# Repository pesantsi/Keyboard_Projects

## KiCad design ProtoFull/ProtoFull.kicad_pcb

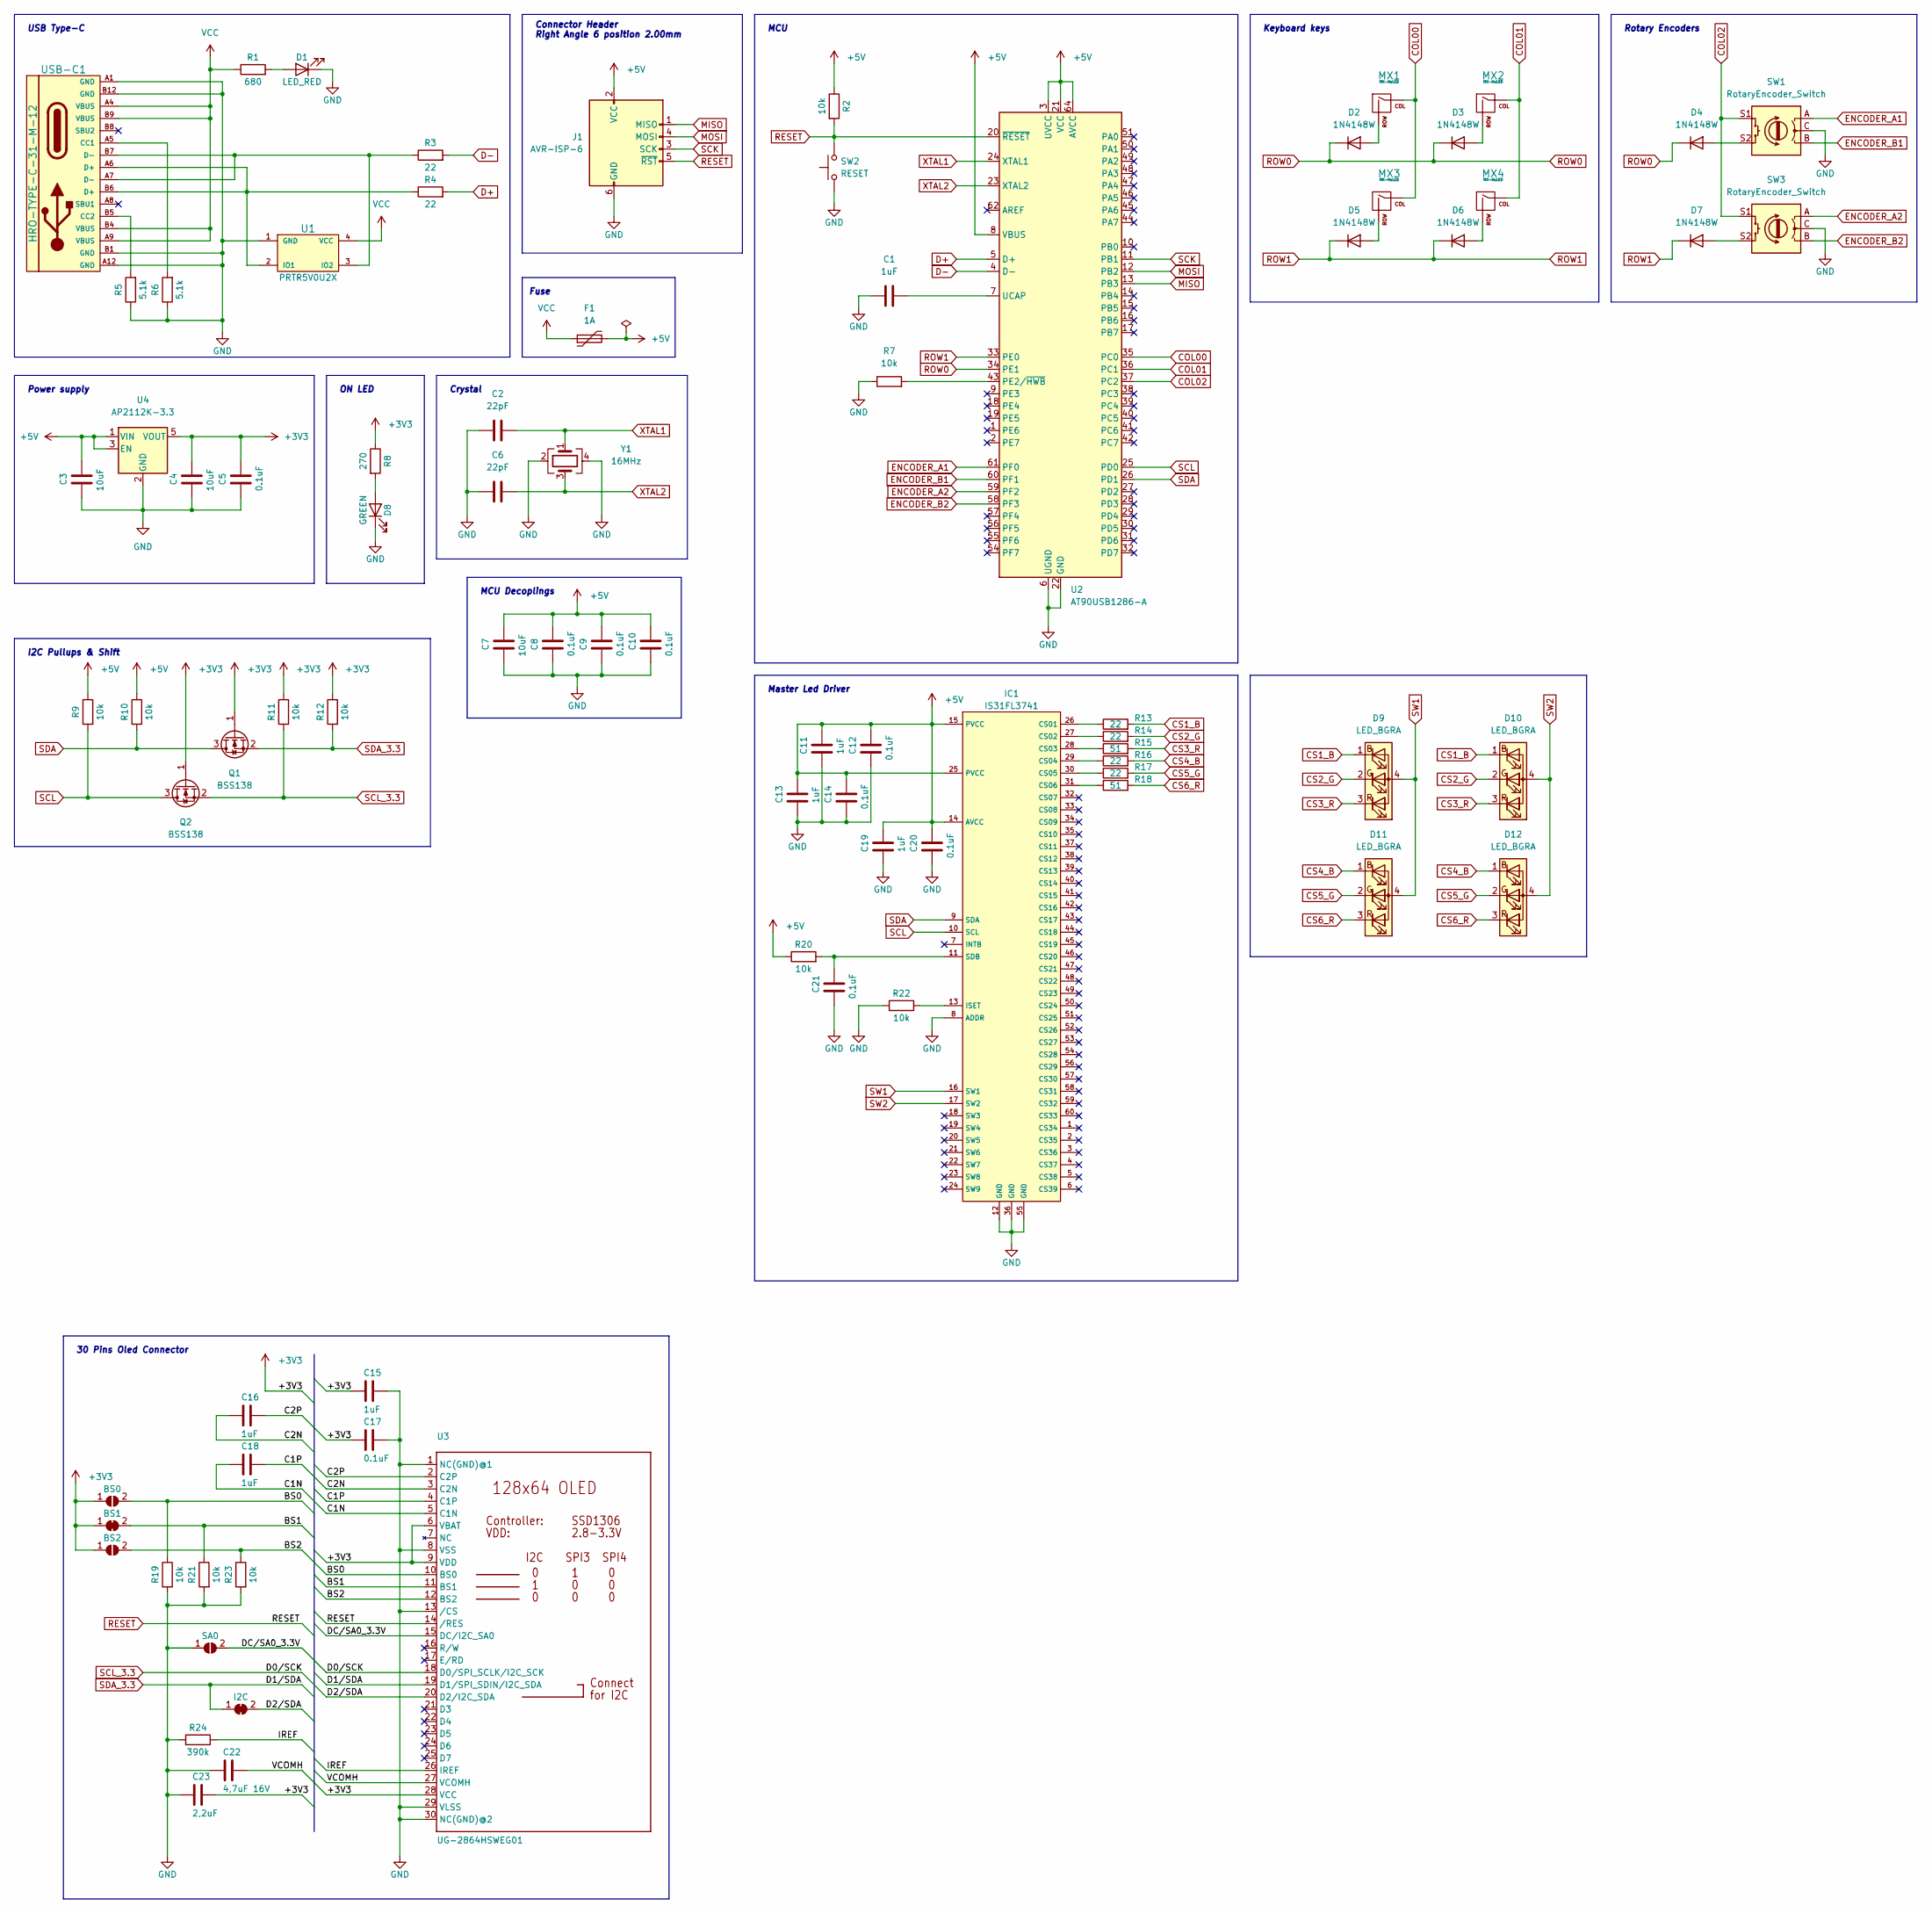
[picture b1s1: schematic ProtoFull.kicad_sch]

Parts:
C1, C11, C13, C19: 1uF; C_0805_2012Metric
C2, C6: 22pF; C_0805_2012Metric
C3, C4, C7: 10uF; C_0805_2012Metric
C5, C8, C9, C10, C12, C14, C20, C21: 0.1uF; C_0805_2012Metric
C15, C16, C18: 1uF; C_0805_2012Metric_Pad1.18x1.45mm_HandSolder
C17: 0.1uF; C_0805_2012Metric_Pad1.18x1.45mm_HandSolder
C22: 4,7uF 16V; C_0805_2012Metric_Pad1.18x1.45mm_HandSolder
C23: 2,2uF; C_0805_2012Metric_Pad1.18x1.45mm_HandSolder
D1: LED_RED; LED_0805_2012Metric_Pad1.15x1.40mm_HandSolder
D2, D3, D4, D5, D6, D7: 1N4148W; D_SOD-123
D8: GREEN; LED_0805_2012Metric_Pad1.15x1.40mm_HandSolder
D9, D10, D11, D12: LED_BGRA; QBLP677R-RGB
F1: 1A; Fuse_1206_3216Metric_Pad1.42x1.75mm_HandSolder
IC1: IS31FL3741; QFN40P700X700X80-61N-D
J1: AVR-ISP-6; Reset_Pretty
JP1: BS0; SolderJumper-2_P1.3mm_Open_RoundedPad1.0x1.5mm
JP2: BS1; SolderJumper-2_P1.3mm_Open_RoundedPad1.0x1.5mm
JP3: BS2; SolderJumper-2_P1.3mm_Open_RoundedPad1.0x1.5mm
JP4: SA0; SolderJumper-2_P1.3mm_Open_RoundedPad1.0x1.5mm
JP5: I2C; SolderJumper-2_P1.3mm_Bridged_RoundedPad1.0x1.5mm
MX1, MX2, MX3, MX4: MX-NoLED; MXOnly-1U-NoLED
Q1, Q2: BSS138; SOT-23
R1: 680; R_0805_2012Metric
R2, R7, R9, R10, R11, R12, R20, R22: 10k; R_0805_2012Metric
R3, R4, R13, R14, R16, R17: 22; R_0805_2012Metric
R5, R6: 5.1k; R_0805_2012Metric
R8: 270; R_0805_2012Metric
R15, R18: 51; R_0805_2012Metric
R19, R21, R23: 10k; R_0805_2012Metric_Pad1.20x1.40mm_HandSolder
R24: 390k; R_0805_2012Metric_Pad1.20x1.40mm_HandSolder
SW1, SW3: RotaryEncoder_Switch; RotaryEncoder_Alps_EC12E-Switch_Vertical_H20mm_CircularMoun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
SW2: RESET; PushButton_6x6mm_TH
U1: PRTR5V0U2X; SOT-143_Handsoldering
U2: AT90USB1286-A; TQFP-64_14x14mm_P0.8mm
U3: UG-2864HSWEG01; 5051103091
U4: AP2112K-3.3; SOT-23-5
USB-C1: HRO-TYPE-C-31-M-12; TYPE-C-31-M-12
Y1: 16MHz; Crystal_SMD_3225-4Pin_3.2x2.5mm_HandSoldering

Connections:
+3V3: C4.1, C5.1, C15.2, C17.2, C23.1, JP1.1 (A), JP2.1 (A), JP3.1 (A), Q1.1 (G), Q2.1 (G), R8.1, R11.1, R12.1, U3.6 (VBAT), U3.9 (VDD), U3.28 (VCC), U4.5 (VOUT)
+5V: C3.1, C7.1, C8.1, C9.1, C10.1, C11.1, C12.1, C13.1, C14.1, C19.1, C20.1, F1.2, IC1.14 (AVCC), IC1.15 (PVCC), IC1.25 (PVCC), J1.2 (VCC), R2.1, R9.1, R10.1, R20.1, U2.3 (UVCC), U2.8 (VBUS), U2.21 (VCC), U2.52 (VCC), U2.64 (AVCC), U4.1 (VIN), U4.3 (EN)
/BS0: JP1.2 (B), R19.1, U3.10 (BS0)
/BS1: JP2.2 (B), R21.1, U3.11 (BS1)
/BS2: JP3.2 (B), R23.1, U3.12 (BS2)
/C1N: C18.2, U3.5 (C1N)
/C1P: C18.1, U3.4 (C1P)
/C2N: C16.2, U3.3 (C2N)
/C2P: C16.1, U3.2 (C2P)
/D2/SDA: JP5.2 (B), U3.20 (D2/I2C_SDA)
/DC/SA0_3.3V: JP4.2 (B), U3.15 (DC/I2C_SA0)
/IREF: R24.1, U3.26 (IREF)
/VCOMH: C22.1, U3.27 (VCOMH)
COL00: MX1.1 (COL), MX3.1 (COL), U2.35 (PC0)
COL01: MX2.1 (COL), MX4.1 (COL), U2.36 (PC1)
COL02: SW1.S1, SW3.S1, U2.37 (PC2)
CS1_B: D9.1 (BK), D10.1 (BK), R13.2
CS2_G: D9.2 (GK), D10.2 (GK), R14.2
CS3_R: D9.3 (RK), D10.3 (RK), R15.2
CS4_B: D11.1 (BK), D12.1 (BK), R16.2
CS5_G: D11.2 (GK), D12.2 (GK), R17.2
CS6_R: D11.3 (RK), D12.3 (RK), R18.2
D+: R4.2, U2.5 (D+)
D-: R3.2, U2.4 (D-)
ENCODER_A1: SW1.A, U2.61 (PF0)
ENCODER_A2: SW3.A, U2.59 (PF2)
ENCODER_B1: SW1.B, U2.60 (PF1)
ENCODER_B2: SW3.B, U2.58 (PF3)
GND: C1.2, C2.1, C3.2, C4.2, C5.2, C6.1, C7.2, C8.2, C9.2, C10.2, C11.2, C12.2, C13.2, C14.2, C15.1, C17.1, C19.2, C20.2, C21.2, C22.2, C23.2, D1.1 (K), D8.1 (K), IC1.8 (ADDR), IC1.12 (GND), IC1.36 (GND), IC1.55 (GND), J1.6 (GND), JP4.1 (A), R5.1, R6.1, R7.1, R19.2, R21.2, R22.2, R23.2, R24.2, SW1.C, SW2.1, SW3.C, U1.1 (GND), U2.6 (UGND), U2.22 (GND), U2.53 (GND), U2.63 (GND), U3.1 (NC(GND)@1), U3.8 (VSS), U3.13 (/CS), U3.29 (VLSS), U3.30 (NC(GND)@2), U4.2 (GND), USB-C1.A1 (GND), USB-C1.A12 (GND), USB-C1.B1 (GND), USB-C1.B12 (GND), Y1.2, Y1.4
MISO: J1.1 (MISO), U2.13 (PB3)
MOSI: J1.4 (MOSI), U2.12 (PB2)
unnamed: C1.1, U2.7 (UCAP)
unnamed: C21.1, IC1.11 (SDB), R20.2
unnamed: D1.2 (A), R1.2
unnamed: D2.2 (A), MX1.2 (ROW)
unnamed: D3.2 (A), MX2.2 (ROW)
unnamed: D4.2 (A), SW1.S2
unnamed: D5.2 (A), MX3.2 (ROW)
unnamed: D6.2 (A), MX4.2 (ROW)
unnamed: D7.2 (A), SW3.S2
unnamed: D8.2 (A), R8.2
unnamed: IC1.13 (ISET), R22.1
unnamed: IC1.26 (CS01), R13.1
unnamed: IC1.27 (CS02), R14.1
unnamed: IC1.28 (CS03), R15.1
unnamed: IC1.29 (CS04), R16.1
unnamed: IC1.30 (CS05), R17.1
unnamed: IC1.31 (CS06), R18.1
unnamed: R3.1, U1.3 (IO2), USB-C1.A7 (D-), USB-C1.B7 (D-)
unnamed: R4.1, U1.2 (IO1), USB-C1.A6 (D+), USB-C1.B6 (D+)
unnamed: R5.2, USB-C1.B5 (CC2)
unnamed: R6.2, USB-C1.A5 (CC1)
unnamed: R7.2, U2.43 (PE2/~HWB)
RESET: J1.5 (~RST), R2.2, SW2.2, U2.20 (~RESET), U3.14 (/RES)
ROW0: D2.1 (K), D3.1 (K), D4.1 (K), U2.34 (PE1)
ROW1: D5.1 (K), D6.1 (K), D7.1 (K), U2.33 (PE0)
SCK: J1.3 (SCK), U2.11 (PB1)
SCL: IC1.10 (SCL), Q2.3 (D), R9.2, U2.25 (PD0)
SCL_3.3: Q2.2 (S), R11.2, U3.18 (D0/SPI_SCLK/I2C_SCK)
SDA: IC1.9 (SDA), Q1.3 (D), R10.2, U2.26 (PD1)
SDA_3.3: JP5.1 (A), Q1.2 (S), R12.2, U3.19 (D1/SPI_SDIN/I2C_SDA)
SW1: D9.4 (A), D11.4 (A), IC1.16 (SW1)
SW2: D10.4 (A), D12.4 (A), IC1.17 (SW2)
VCC: F1.1, R1.1, U1.4 (VCC), USB-C1.A4 (VBUS), USB-C1.A9 (VBUS), USB-C1.B4 (VBUS), USB-C1.B9 (VBUS)
XTAL1: C2.2, U2.24 (XTAL1), Y1.1
XTAL2: C6.2, U2.23 (XTAL2), Y1.3

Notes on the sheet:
USB Type-C
Rotary Encoders
MCU Decoplings
I2C Pullups & Shift
ON LED
Fuse
Keyboard keys
Connector Header Right Angle 6 position 2.00mm
MCU
Crystal
Power supply
Master Led Driver
30 Pins Oled Connector

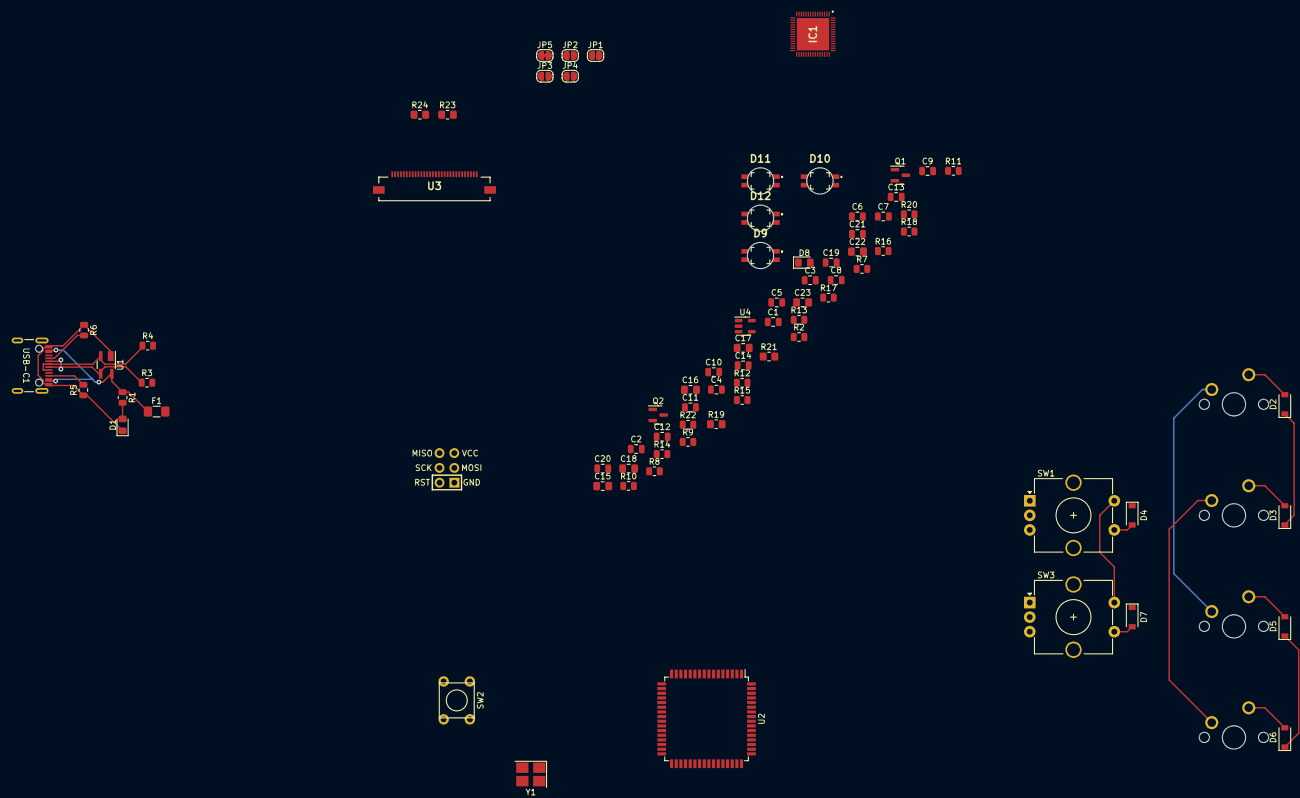
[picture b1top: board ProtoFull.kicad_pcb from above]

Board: 2 copper layers, 82 parts (0 on the bottom side), 66 nets.

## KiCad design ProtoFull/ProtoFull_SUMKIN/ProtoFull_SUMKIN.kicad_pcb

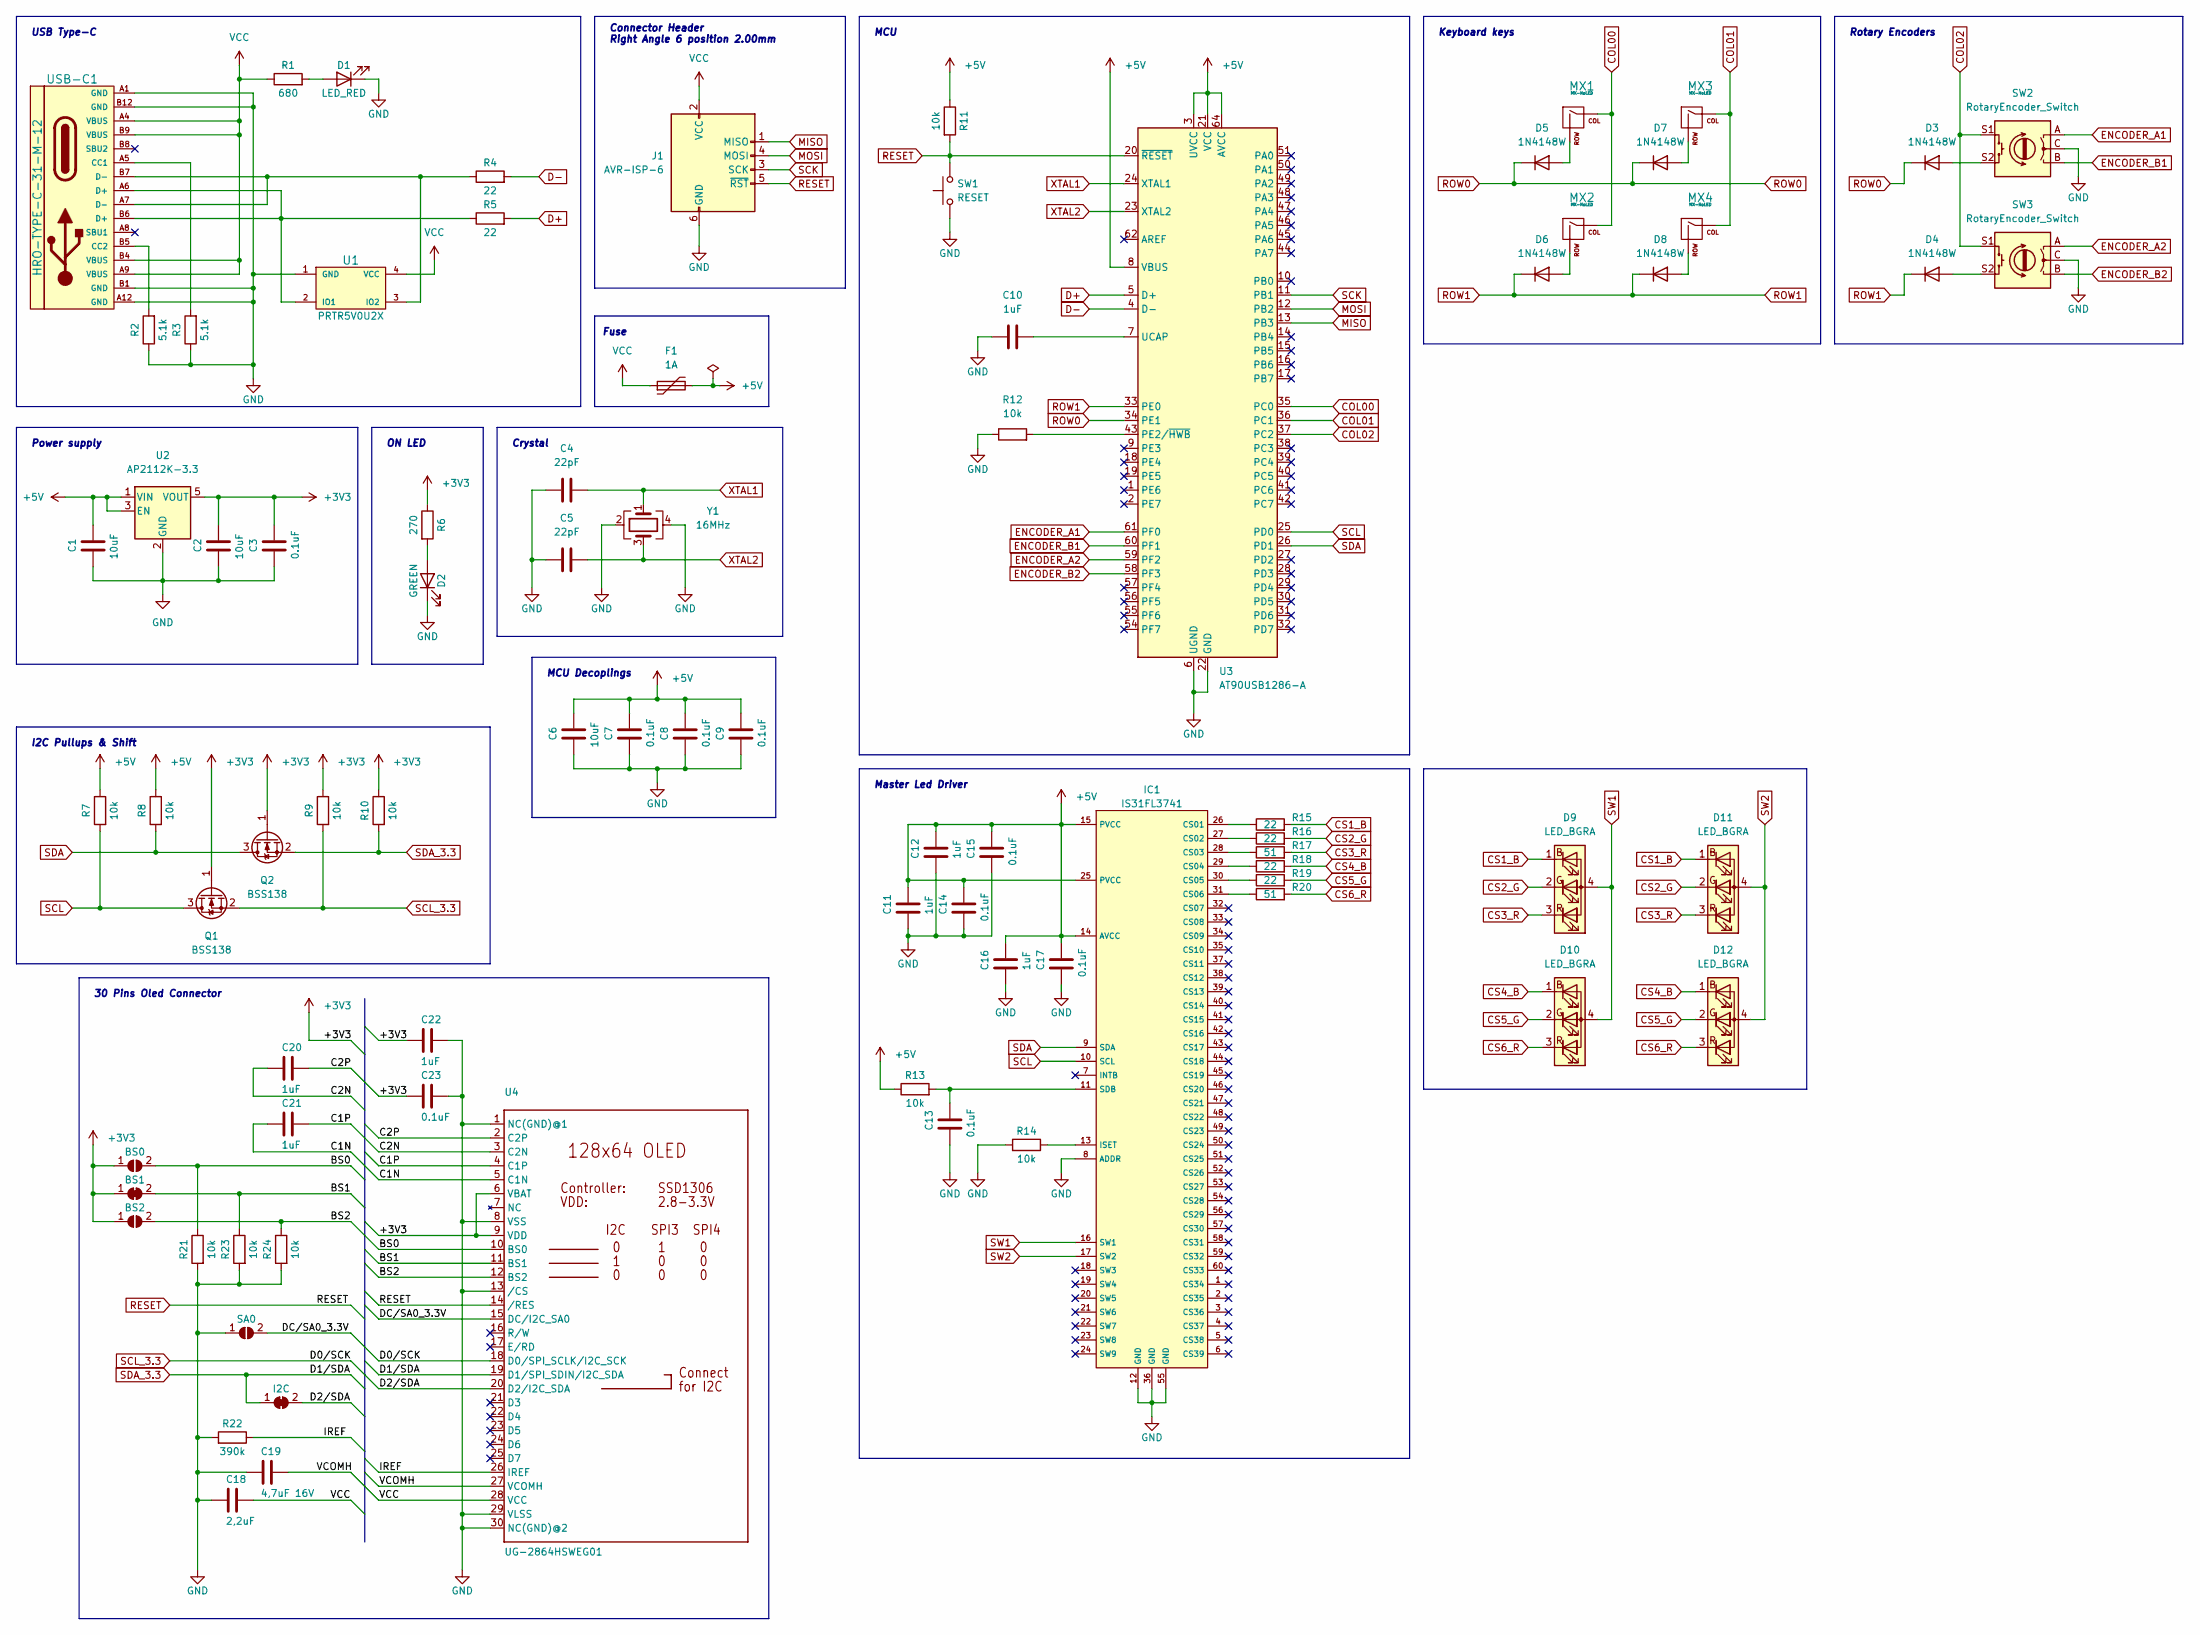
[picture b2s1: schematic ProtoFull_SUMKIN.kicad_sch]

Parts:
C1, C2, C6: 10uF; C_0805_2012Metric_Pad1.18x1.45mm_HandSolder
C3, C7, C8, C9, C13, C14, C15, C17, C23: 0.1uF; C_0805_2012Metric_Pad1.18x1.45mm_HandSolder
C4, C5: 22pF; C_0805_2012Metric_Pad1.18x1.45mm_HandSolder
C10, C11, C12, C16, C20, C21, C22: 1uF; C_0805_2012Metric_Pad1.18x1.45mm_HandSolder
C18: 2,2uF; C_0805_2012Metric_Pad1.18x1.45mm_HandSolder
C19: 4,7uF 16V; C_0805_2012Metric_Pad1.18x1.45mm_HandSolder
D1: LED_RED; LED_0805_2012Metric_Pad1.15x1.40mm_HandSolder
D2: GREEN; LED_0805_2012Metric_Pad1.15x1.40mm_HandSolder
D3, D4, D5, D6, D7, D8: 1N4148W; D_SOD-123
D9, D10, D11, D12: LED_BGRA; QBLP677R-RGB_RoundCutout
F1: 1A; Fuse_1206_3216Metric_Pad1.42x1.75mm_HandSolder
IC1: IS31FL3741; QFN-60_EP_7x7_Pitch0.4mm
J1: AVR-ISP-6; SWR204NRTND03STGA
JP1: BS0; SolderJumper-2_P1.3mm_Open_RoundedPad1.0x1.5mm
JP2: BS1; SolderJumper-2_P1.3mm_Open_RoundedPad1.0x1.5mm
JP3: BS2; SolderJumper-2_P1.3mm_Open_RoundedPad1.0x1.5mm
JP4: SA0; SolderJumper-2_P1.3mm_Open_RoundedPad1.0x1.5mm
JP5: I2C; SolderJumper-2_P1.3mm_Bridged_RoundedPad1.0x1.5mm
MX1, MX2, MX3, MX4: MX-NoLED; MXOnly-1U-NoLED
Q1, Q2: BSS138; SOT-23
R1: 680; R_0805_2012Metric
R2, R3: 5.1k; R_0805_2012Metric
R4, R5: 22; R_0805_2012Metric
R6: 270; R_0805_2012Metric
R7, R8, R9, R10: 10k; R_0805_2012Metric
R11, R12, R13, R14, R21, R23, R24: 10k; R_0805_2012Metric_Pad1.20x1.40mm_HandSolder
R15, R16, R18, R19: 22; R_0805_2012Metric_Pad1.20x1.40mm_HandSolder
R17, R20: 51; R_0805_2012Metric_Pad1.20x1.40mm_HandSolder
R22: 390k; R_0805_2012Metric_Pad1.20x1.40mm_HandSolder
SW1: RESET; SKQG-1155865
SW2, SW3: RotaryEncoder_Switch; RotaryEncoder_Alps_EC12E-Switch_Vertical_H20mm_CircularMoun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
U1: PRTR5V0U2X; SOT-143_Handsoldering
U2: AP2112K-3.3; SOT-23-5
U3: AT90USB1286-A; TQFP-64_14x14mm_P0.8mm
U4: UG-2864HSWEG01; 5051103091
USB-C1: HRO-TYPE-C-31-M-12; TYPE-C-31-M-12
Y1: 16MHz; Crystal_SMD_3225-4Pin_3.2x2.5mm_HandSoldering

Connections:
+3V3: C2.1, C3.1, C22.2, C23.2, JP1.1 (A), JP2.1 (A), JP3.1 (A), Q1.1 (G), Q2.1 (G), R6.1, R9.1, R10.1, U2.5 (VOUT), U4.6 (VBAT), U4.9 (VDD)
+5V: C1.1, C6.1, C7.1, C8.1, C9.1, F1.2, R7.1, R8.1, R11.1, R13.1, U2.1 (VIN), U2.3 (EN), U3.3 (UVCC), U3.8 (VBUS), U3.21 (VCC), U3.52 (VCC), U3.64 (AVCC)
/BS0: JP1.2 (B), R21.1, U4.10 (BS0)
/BS1: JP2.2 (B), R23.1, U4.11 (BS1)
/BS2: JP3.2 (B), R24.1, U4.12 (BS2)
/C1N: C21.2, U4.5 (C1N)
/C1P: C21.1, U4.4 (C1P)
/C2N: C20.2, U4.3 (C2N)
/C2P: C20.1, U4.2 (C2P)
/D2/SDA: JP5.2 (B), U4.20 (D2/I2C_SDA)
/DC/SA0_3.3V: JP4.2 (B), U4.15 (DC/I2C_SA0)
/IREF: R22.1, U4.26 (IREF)
/VCOMH: C19.1, U4.27 (VCOMH)
COL00: MX1.1 (COL), MX2.1 (COL), U3.35 (PC0)
COL01: MX3.1 (COL), MX4.1 (COL), U3.36 (PC1)
COL02: SW2.S1, SW3.S1, U3.37 (PC2)
CS1_B: D9.1 (BK), D11.1 (BK), R15.2
CS2_G: D9.2 (GK), D11.2 (GK), R16.2
CS3_R: D9.3 (RK), D11.3 (RK), R17.2
CS4_B: D10.1 (BK), D12.1 (BK), R18.2
CS5_G: D10.2 (GK), D12.2 (GK), R19.2
CS6_R: D10.3 (RK), D12.3 (RK), R20.2
D+: R5.2, U3.5 (D+)
D-: R4.2, U3.4 (D-)
ENCODER_A1: SW2.A, U3.61 (PF0)
ENCODER_A2: SW3.A, U3.59 (PF2)
ENCODER_B1: SW2.B, U3.60 (PF1)
ENCODER_B2: SW3.B, U3.58 (PF3)
GND: C1.2, C2.2, C3.2, C4.1, C5.1, C6.2, C7.2, C8.2, C9.2, C10.2, C11.2, C12.2, C13.2, C14.2, C15.2, C16.2, C17.2, C18.2, C19.2, C22.1, C23.1, D1.1 (K), D2.1 (K), IC1.8 (ADDR), IC1.12 (GND), IC1.36 (GND), IC1.55 (GND), J1.6 (GND), JP4.1 (A), R2.1, R3.1, R12.1, R14.2, R21.2, R22.2, R23.2, R24.2, SW1.1, SW2.C, SW3.C, U1.1 (GND), U2.2 (GND), U3.6 (UGND), U3.22 (GND), U3.53 (GND), U3.63 (GND), U4.1 (NC(GND)@1), U4.8 (VSS), U4.13 (/CS), U4.29 (VLSS), U4.30 (NC(GND)@2), USB-C1.A1 (GND), USB-C1.A12 (GND), USB-C1.B1 (GND), USB-C1.B12 (GND), Y1.2, Y1.4
MISO: J1.1 (MISO), U3.13 (PB3)
MOSI: J1.4 (MOSI), U3.12 (PB2)
unnamed: C10.1, U3.7 (UCAP)
unnamed: C13.1, IC1.11 (SDB), R13.2
unnamed: D1.2 (A), R1.2
unnamed: D2.2 (A), R6.2
unnamed: D3.2 (A), SW2.S2
unnamed: D4.2 (A), SW3.S2
unnamed: D5.2 (A), MX1.2 (ROW)
unnamed: D6.2 (A), MX2.2 (ROW)
unnamed: D7.2 (A), MX3.2 (ROW)
unnamed: D8.2 (A), MX4.2 (ROW)
unnamed: IC1.13 (ISET), R14.1
unnamed: IC1.26 (CS01), R15.1
unnamed: IC1.27 (CS02), R16.1
unnamed: IC1.28 (CS03), R17.1
unnamed: IC1.29 (CS04), R18.1
unnamed: IC1.30 (CS05), R19.1
unnamed: IC1.31 (CS06), R20.1
unnamed: R2.2, USB-C1.B5 (CC2)
unnamed: R3.2, USB-C1.A5 (CC1)
unnamed: R4.1, U1.3 (IO2), USB-C1.A7 (D-), USB-C1.B7 (D-)
unnamed: R5.1, U1.2 (IO1), USB-C1.A6 (D+), USB-C1.B6 (D+)
unnamed: R12.2, U3.43 (PE2/~HWB)
RESET: J1.5 (~RST), R11.2, SW1.2, U3.20 (~RESET), U4.14 (/RES)
ROW0: D3.1 (K), D5.1 (K), D7.1 (K), U3.34 (PE1)
ROW1: D4.1 (K), D6.1 (K), D8.1 (K), U3.33 (PE0)
SCK: J1.3 (SCK), U3.11 (PB1)
SCL: IC1.10 (SCL), Q1.3 (D), R7.2, U3.25 (PD0)
SCL_3.3: Q1.2 (S), R9.2, U4.18 (D0/SPI_SCLK/I2C_SCK)
SDA: IC1.9 (SDA), Q2.3 (D), R8.2, U3.26 (PD1)
SDA_3.3: JP5.1 (A), Q2.2 (S), R10.2, U4.19 (D1/SPI_SDIN/I2C_SDA)
SW1: D9.4 (A), D10.4 (A), IC1.16 (SW1)
SW2: D11.4 (A), D12.4 (A), IC1.17 (SW2)
VCC: C18.1, F1.1, J1.2 (VCC), R1.1, U1.4 (VCC), U4.28 (VCC), USB-C1.A4 (VBUS), USB-C1.A9 (VBUS), USB-C1.B4 (VBUS), USB-C1.B9 (VBUS)
XTAL1: C4.2, U3.24 (XTAL1), Y1.1
XTAL2: C5.2, U3.23 (XTAL2), Y1.3

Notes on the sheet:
Keyboard keys
I2C Pullups & Shift
Connector Header Right Angle 6 position 2.00mm
30 Pins Oled Connector
Crystal
Power supply
USB Type-C
Master Led Driver
Rotary Encoders
MCU
Fuse
ON LED
MCU Decoplings

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
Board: 2 copper layers, 82 parts (0 on the bottom side), 68 nets, no tracks yet.

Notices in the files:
parts and their libraries:
Copyright 2021 Accelerated Designs. All rights reserved.
